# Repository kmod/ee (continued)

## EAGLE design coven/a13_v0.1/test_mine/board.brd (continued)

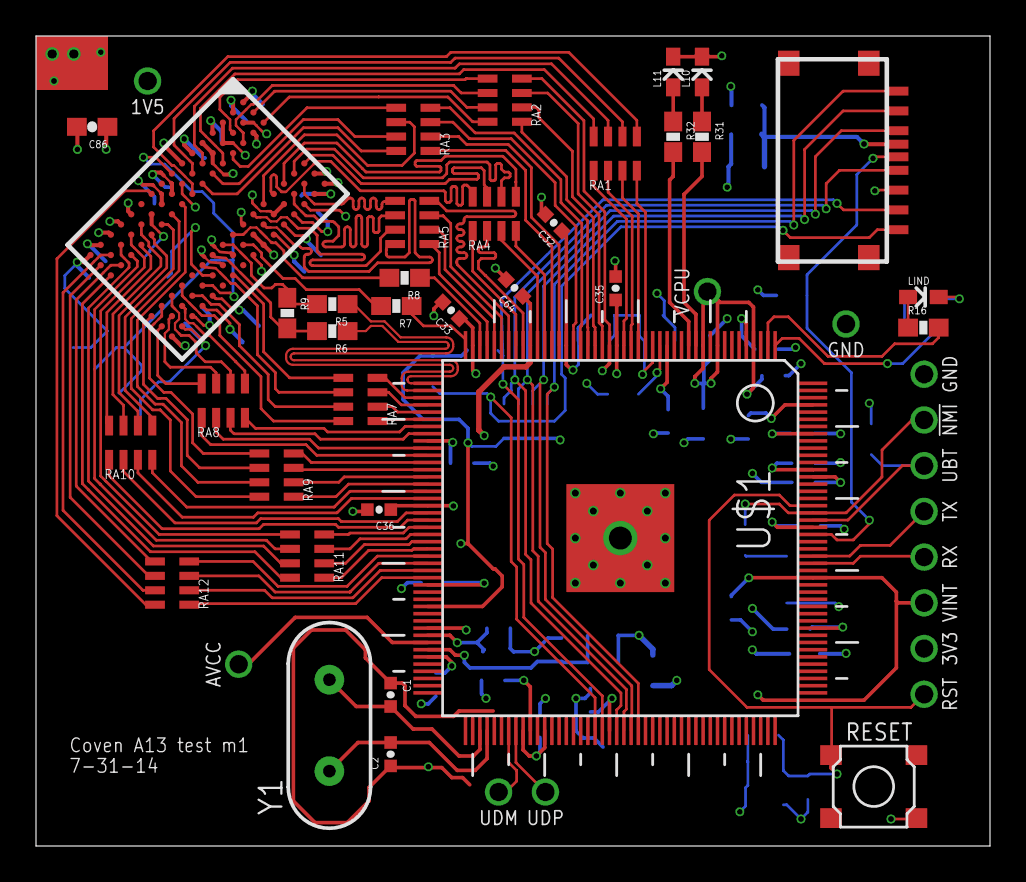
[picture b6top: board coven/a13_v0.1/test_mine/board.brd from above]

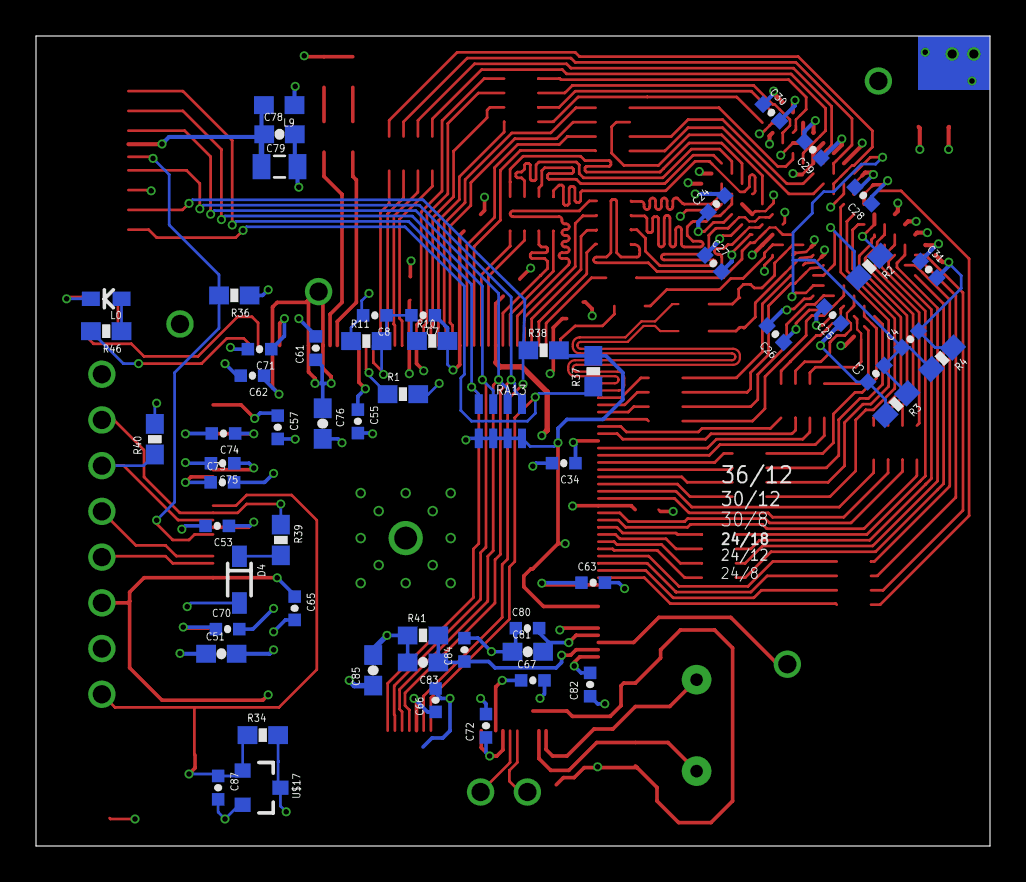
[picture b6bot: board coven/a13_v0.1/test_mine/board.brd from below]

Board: 4 copper layers, 53.0 x 45.0 mm, 108 parts (58 on the bottom side), 135 nets.

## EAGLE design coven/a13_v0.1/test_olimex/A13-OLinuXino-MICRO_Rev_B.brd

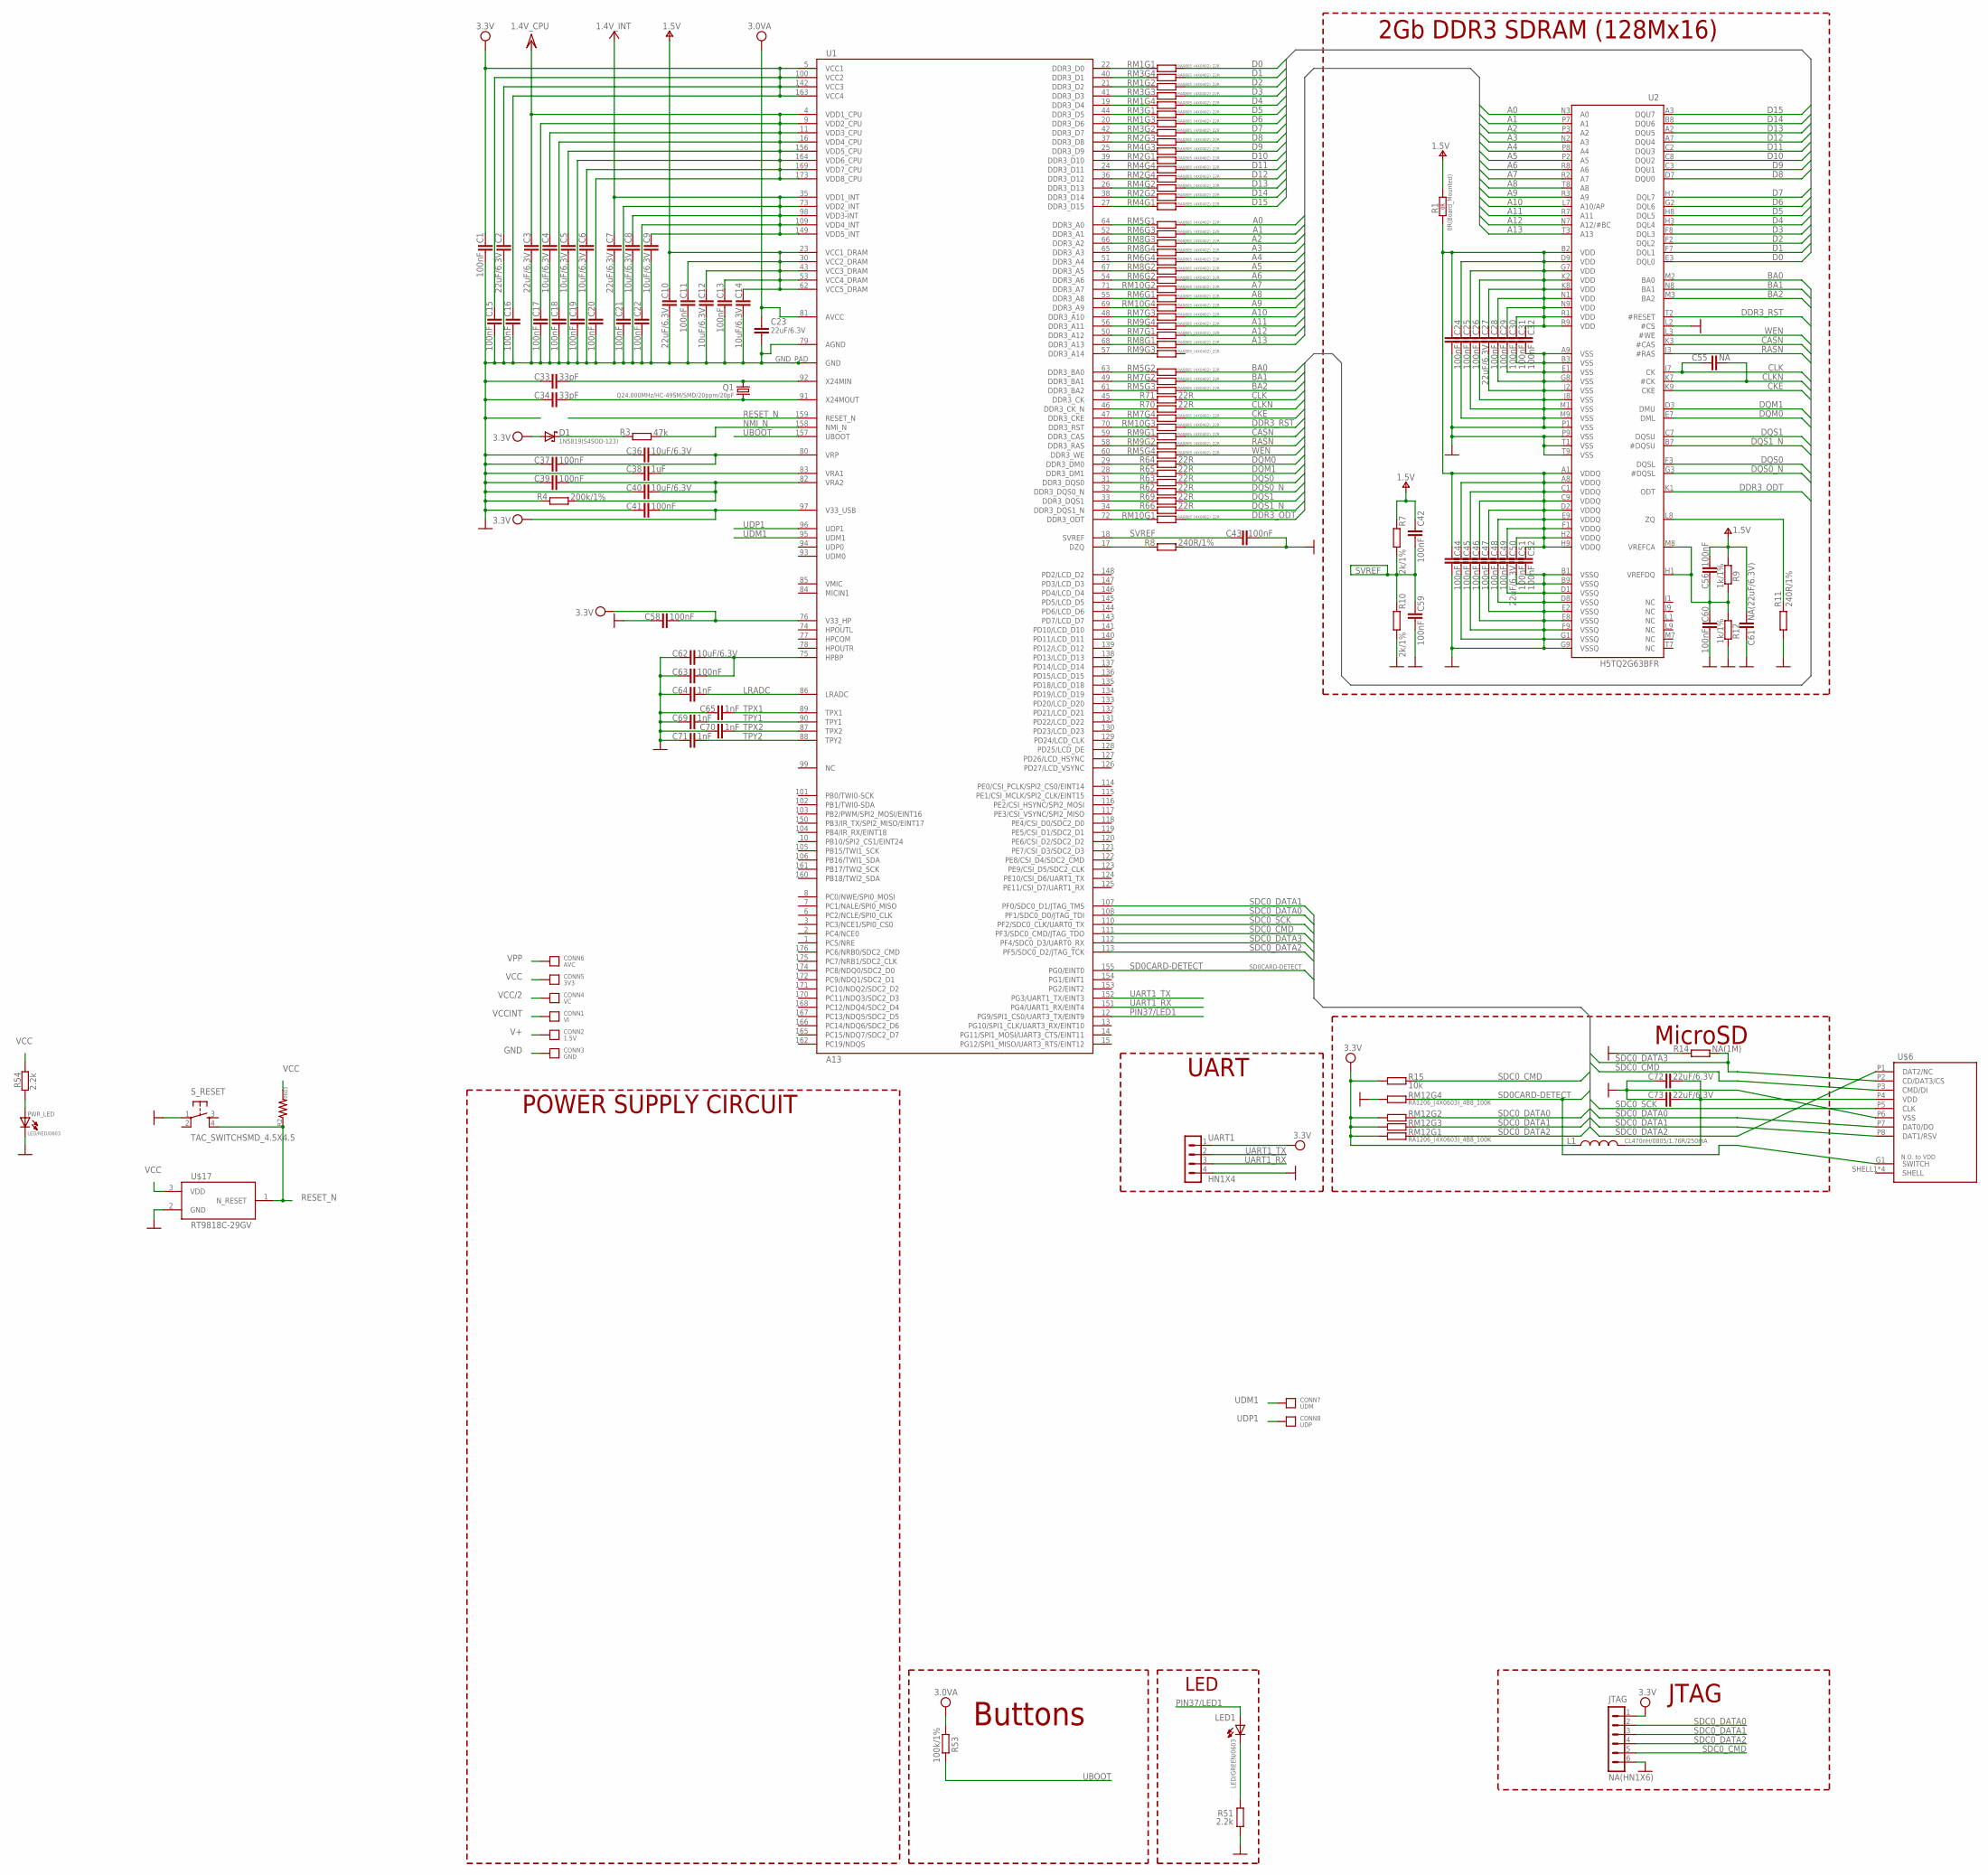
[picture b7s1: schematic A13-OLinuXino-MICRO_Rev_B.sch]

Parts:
C1, C11, C13, C15, C16, C17, C18, C19, C20, C21, C22, C24, C25, C26, C28, C29, C30, C31, C32, C37, C39, C41, C42, C43, C44, C45, C46, C47, C48, C49, C51, C52, C56, C58, C59, C60, C63: 100nF; C0402
C2, C3, C7, C10, C23, C27, C50, C72, C73: 22uF/6.3V; C0603_DWS
C4, C5, C6, C8, C9, C12, C14, C36, C40, C62: 10uF/6.3V; C0603_DWS
C33, C34: 33pF; C0402
C38: 1uF; C0402
C55: NA; C0603_DWS
C61: NA(22uF/6.3V); C0603_DWS
C64, C65, C69, C70, C71: 1nF; C0402
CONN1: VI; HOLE_22AWG
CONN2: 1.5V; HOLE_22AWG
CONN3: GND; HOLE_22AWG
CONN4: VC; HOLE_22AWG
CONN5: 3V3; HOLE_22AWG
CONN6: AVC; HOLE_22AWG
CONN7: UDM; HOLE_22AWG
CONN8: UDP; HOLE_22AWG
D1: 1N5819(S4SOD-123); SOD-123
JTAG: NA(HN1X6); HN1X6
L1: CL470nH/0805/1.76R/250mA; L0805_5MIL_DWS
LED1: LED/GREEN/0603; LED-0603
PWR_LED: LED/RED/0603; LED-0603
Q1: Q24.000MHz/HC-49SM/SMD/20ppm/20pF; HC49/SMD2_THIN
R1: 0R(Board_Mounted); 0603_0R
R2: RESISTOR0603; 0603-RES
R3: 47k; R0603_5MIL_DWS
R4: 200k/1%; R0603_5MIL_DWS
R7, R10: 2k/1%; R0603_5MIL_DWS
R8, R11: 240R/1%; R0603_5MIL_DWS
R9, R12: 1k/1%; R0603_5MIL_DWS
R14: NA(1M); R0603_5MIL_DWS
R15: 10k; R0603_5MIL_DWS
R51, R54: 2.2k; R0603_5MIL_DWS
R53: 100k/1%; R0603_5MIL_DWS
R62, R63, R64, R65, R66, R69, R70, R71: 22R; R0603_5MIL_DWS
RM1, RM2, RM3, RM4, RM5, RM6, RM7, RM8, RM9, RM10: RA0805_(4X0402)_22R; R_MATRIX_4_0402_25X625
RM12: RA1206_(4X0603)_4B8_100K; R_MATRIX_4
S_RESET: TAC_SWITCHSMD_4.5X4.5; TAC_SWITCH_SMD_4.5X4.5
U1: A13; TQFP176
U2: H5TQ2G63BFR; FBGA96
U$6: MICROSDMOLEX-1050270001; MICROSD-MOLEX-1050270001
U$17: RT9818C-29GV; SOT23-3
UART1: HN1X4

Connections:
A0: RM5.1.2 (2), U2.N3 (A0)
A1: RM6.3.2 (2), U2.P7 (A1)
A2: RM8.3.2 (2), U2.P3 (A2)
A3: RM8.4.2 (2), U2.N2 (A3)
A4: RM6.4.2 (2), U2.P8 (A4)
A5: RM8.2.2 (2), U2.P2 (A5)
A6: RM6.2.2 (2), U2.R8 (A6)
A7: RM10.2.2 (2), U2.R2 (A7)
A8: RM6.1.2 (2), U2.T8 (A8)
A9: RM10.4.2 (2), U2.R3 (A9)
A10: RM7.3.2 (2), U2.L7 (A10/AP)
A11: RM9.4.2 (2), U2.R7 (A11)
A12: RM7.1.2 (2), U2.N7 (A12/#BC)
A13: RM8.1.2 (2), U2.T3 (A13)
BA0: RM5.2.2 (2), U2.M2 (BA0)
BA1: RM7.2.2 (2), U2.N8 (BA1)
BA2: RM5.3.2 (2), U2.M3 (BA2)
CASN: RM9.1.2 (2), U2.K3 (#CAS)
CKE: RM7.4.2 (2), U2.K9 (CKE)
CLK: C55.1, R71.1, U2.J7 (CK)
CLKN: C55.2, R70.1, U2.K7 (#CK)
D0: RM1.1.2 (2), U2.E3 (DQL0)
D1: RM3.4.2 (2), U2.F7 (DQL1)
D2: RM1.2.2 (2), U2.F2 (DQL2)
D3: RM3.3.2 (2), U2.F8 (DQL3)
D4: RM1.4.2 (2), U2.H3 (DQL4)
D5: RM3.1.2 (2), U2.H8 (DQL5)
D6: RM1.3.2 (2), U2.G2 (DQL6)
D7: RM3.2.2 (2), U2.H7 (DQL7)
D8: RM2.3.2 (2), U2.D7 (DQU0)
D9: RM4.3.2 (2), U2.C3 (DQU1)
D10: RM2.1.2 (2), U2.C8 (DQU2)
D11: RM4.4.2 (2), U2.C2 (DQU3)
D12: RM2.4.2 (2), U2.A7 (DQU4)
D13: RM4.2.2 (2), U2.A2 (DQU5)
D14: RM2.2.2 (2), U2.B8 (DQU6)
D15: RM4.1.2 (2), U2.A3 (DQU7)
DDR3_A0: RM5.1.1 (1), U1.64 (DDR3_A0)
DDR3_A1: RM6.3.1 (1), U1.52 (DDR3_A1)
DDR3_A2: RM8.3.1 (1), U1.66 (DDR3_A2)
DDR3_A3: RM8.4.1 (1), U1.65 (DDR3_A3)
DDR3_A4: RM6.4.1 (1), U1.51 (DDR3_A4)
DDR3_A5: RM8.2.1 (1), U1.67 (DDR3_A5)
DDR3_A6: RM6.2.1 (1), U1.54 (DDR3_A6)
DDR3_A7: RM10.2.1 (1), U1.71 (DDR3_A7)
DDR3_A8: RM6.1.1 (1), U1.55 (DDR3_A8)
DDR3_A9: RM10.4.1 (1), U1.69 (DDR3_A9)
DDR3_A10: RM7.3.1 (1), U1.48 (DDR3_A10)
DDR3_A11: RM9.4.1 (1), U1.56 (DDR3_A11)
DDR3_A12: RM7.1.1 (1), U1.50 (DDR3_A12)
DDR3_A13: RM8.1.1 (1), U1.68 (DDR3_A13)
DDR3_A14: RM9.3.1 (1), U1.57 (DDR3_A14)
DDR3_BA0: RM5.2.1 (1), U1.63 (DDR3_BA0)
DDR3_BA1: RM7.2.1 (1), U1.49 (DDR3_BA1)
DDR3_BA2: RM5.3.1 (1), U1.61 (DDR3_BA2)
DDR3_CAS: RM9.1.1 (1), U1.59 (DDR3_CAS)
DDR3_CK: R71.2, U1.45 (DDR3_CK)
DDR3_CKE: RM7.4.1 (1), U1.47 (DDR3_CKE)
DDR3_CK_N: R70.2, U1.46 (DDR3_CK_N)
DDR3_D0: RM1.1.1 (1), U1.22 (DDR3_D0)
DDR3_D1: RM3.4.1 (1), U1.40 (DDR3_D1)
DDR3_D2: RM1.2.1 (1), U1.21 (DDR3_D2)
DDR3_D3: RM3.3.1 (1), U1.41 (DDR3_D3)
DDR3_D4: RM1.4.1 (1), U1.19 (DDR3_D4)
DDR3_D5: RM3.1.1 (1), U1.44 (DDR3_D5)
DDR3_D6: RM1.3.1 (1), U1.20 (DDR3_D6)
DDR3_D7: RM3.2.1 (1), U1.42 (DDR3_D7)
DDR3_D8: RM2.3.1 (1), U1.37 (DDR3_D8)
DDR3_D9: RM4.3.1 (1), U1.25 (DDR3_D9)
DDR3_D10: RM2.1.1 (1), U1.39 (DDR3_D10)
DDR3_D11: RM4.4.1 (1), U1.24 (DDR3_D11)
DDR3_D12: RM2.4.1 (1), U1.36 (DDR3_D12)
DDR3_D13: RM4.2.1 (1), U1.26 (DDR3_D13)
DDR3_D14: RM2.2.1 (1), U1.38 (DDR3_D14)
DDR3_D15: RM4.1.1 (1), U1.27 (DDR3_D15)
DDR3_DM0: R64.2, U1.29 (DDR3_DM0)
DDR3_DM1: R65.2, U1.28 (DDR3_DM1)
DDR3_DQS0: R63.2, U1.31 (DDR3_DQS0)
DDR3_DQS0_N: R62.2, U1.32 (DDR3_DQS0_N)
DDR3_DQS1: R69.2, U1.33 (DDR3_DQS1)
DDR3_DQS1_N: R66.2, U1.34 (DDR3_DQS1_N)
DDR3_ODT: RM10.1.2 (2), U2.K1 (ODT)
DDR3_ODTT: RM10.1.1 (1), U1.72 (DDR3_ODT)
DDR3_RAS: RM9.2.1 (1), U1.58 (DDR3_RAS)
DDR3_RST: RM10.3.2 (2), U2.T2 (#RESET)
DDR3_RSTT: RM10.3.1 (1), U1.70 (DDR3_RST)
DDR3_WE: RM5.4.1 (1), U1.60 (DDR3_WE)
DQM0: R64.1, U2.E7 (DML)
DQM1: R65.1, U2.D3 (DMU)
DQS0: R63.1, U2.F3 (DQSL)
DQS0_N: R62.1, U2.G3 (#DQSL)
DQS1: R69.1, U2.C7 (DQSU)
DQS1_N: R66.1, U2.B7 (#DQSU)
DZQ: R8.2, U1.17 (DZQ)
GND: C1.1, C2.1, C3.1, C4.1, C5.1, C6.1, C7.1, C8.1, C9.1, C10.1, C11.1, C12.1, C13.1, C14.1, C15.1, C16.1, C17.1, C18.1, C19.1, C20.1, C21.1, C22.1, C23.1, C24.2, C25.2, C26.2, C27.2, C28.2, C29.2, C30.2, C31.2, C32.2, C33.1, C34.1, C36.1, C37.1, C38.1, C39.1, C40.1, C41.1, C43.1, C44.2, C45.2, C46.2, C47.2, C48.2, C49.2, C50.2, C51.2, C52.2, C58.1, C59.1, C60.1, C61.1, C62.1, C63.1, C64.1, C65.1, C69.1, C70.1, C71.1, C72.1, C73.1, CONN3.P, JTAG.6, PWR_LED.C, R4.2, R8.1, R10.1, R11.1, R12.1, R14.2, R51.1, RM12.4.1 (1), S_RESET.1, U1.79 (AGND), U1.GND_PAD (GND), U1.P$2 (GND), U1.P$3 (GND), U1.P$4 (GND), U1.P$5 (GND), U1.P$6 (GND), U1.P$7 (GND), U1.P$8 (GND), U1.P$9 (GND), U1.P$10 (GND), U1.P$11 (GND), U1.P$12 (GND), U1.P$13 (GND), U1.P$14 (GND), U1.P$15 (GND), U1.P$16 (GND), U1.P$17 (GND), U1.P$18 (GND), U2.A9 (VSS), U2.B1 (VSSQ), U2.B3 (VSS), U2.B9 (VSSQ), U2.D1 (VSSQ), U2.D8 (VSSQ), U2.E1 (VSS), U2.E2 (VSSQ), U2.E8 (VSSQ), U2.F9 (VSSQ), U2.G1 (VSSQ), U2.G8 (VSS), U2.G9 (VSSQ), U2.J2 (VSS), U2.J8 (VSS), U2.L2 (#CS), U2.M1 (VSS), U2.M9 (VSS), U2.P1 (VSS), U2.P9 (VSS), U2.T1 (VSS), U2.T9 (VSS), U$6.P6 (VSS), U$17.2 (GND), UART1.4
LRADC: C64.2, U1.86 (LRADC)
unnamed: C62.2, C63.2, U1.75 (HPBP)
unnamed: C36.2, C37.2, U1.80 (VRP)
unnamed: D1.C, R3.2
unnamed: C38.2, U1.83 (VRA1)
unnamed: C39.2, C40.2, R4.1, U1.82 (VRA2)
unnamed: C56.2, C60.2, R9.1, R12.2, U2.H1 (VREFDQ), U2.M8 (VREFCA)
unnamed: LED1.C, R51.2
unnamed: PWR_LED.A, R54.2
NMI_N: R3.1, U1.158 (NMI_N)
PIN37/LED1: LED1.A, U1.12 (PG9/SPI1_CS0/UART3_TX/EINT9)
RASN: RM9.2.2 (2), U2.J3 (#RAS)
RESET_N: R2.1, S_RESET.4, U1.159 (RESET_N), U$17.1 (N_RESET)
SD0CARD-DETECT: RM12.4.2 (2), U1.155 (PG0/EINT0), U$6.G1 (SWITCH)
SDC0_CMD: JTAG.5, R15.1, U1.111 (PF3/SDC0_CMD/JTAG_TDO), U$6.P3 (CMD/DI)
SDC0_DATA0: JTAG.2, RM12.2.1 (1), U1.108 (PF1/SDC0_D0/JTAG_TDI), U$6.P7 (DAT0/DO)
SDC0_DATA1: JTAG.3, RM12.3.1 (1), U1.107 (PF0/SDC0_D1/JTAG_TMS), U$6.P8 (DAT1/RSV)
SDC0_DATA2: JTAG.4, RM12.1.1 (1), U1.113 (PF5/SDC0_D2/JTAG_TCK), U$6.P1 (DAT2/NC)
SDC0_DATA3: R14.1, U1.112 (PF4/SDC0_D3/UART0_RX), U$6.P2 (CD/DAT3/CS)
SDC0_SCK: U1.110 (PF2/SDC0_CLK/UART0_TX), U$6.P5 (CLK)
SD_VCC: C72.2, C73.2, L1.2, U$6.P4 (VDD)
SVREF: C42.2, C43.2, C59.2, R7.1, R10.2, U1.18 (SVREF)
TPX1: C65.2, U1.89 (TPX1)
TPX2: C70.2, U1.87 (TPX2)
TPY1: C69.2, U1.90 (TPY1)
TPY2: C71.2, U1.88 (TPY2)
UART1_RX: U1.151 (PG4/UART1_RX/EINT4), UART1.3
UART1_TX: U1.152 (PG3/UART1_TX/EINT3), UART1.2
UBOOT: R53.2, U1.157 (UBOOT)
UDM1: CONN7.P, U1.95 (UDM1)
UDP1: CONN8.P, U1.96 (UDP1)
V+: C10.2, C11.2, C12.2, C13.2, C14.2, C42.1, C56.1, C61.2, CONN2.P, R1.1 (1.1), R7.2, R9.2, U1.23 (VCC1_DRAM), U1.30 (VCC2_DRAM), U1.43 (VCC3_DRAM), U1.53 (VCC4_DRAM), U1.62 (VCC5_DRAM)
VCC: C1.2, C2.2, C15.2, C16.2, C41.2, C58.2, CONN5.P, D1.A, JTAG.1, L1.1, R2.2, R15.2, R54.1, RM12.1.2 (2), RM12.2.2 (2), RM12.3.2 (2), U1.5 (VCC1), U1.76 (V33_HP), U1.97 (V33_USB), U1.100 (VCC2), U1.142 (VCC3), U1.163 (VCC4), U$17.3 (VDD), UART1.1
VCC/2: C3.2, C4.2, C5.2, C6.2, C17.2, C18.2, C19.2, C20.2, CONN4.P, U1.4 (VDD1_CPU), U1.9 (VDD2_CPU), U1.11 (VDD3_CPU), U1.16 (VDD4_CPU), U1.156 (VDD5_CPU), U1.164 (VDD6_CPU), U1.169 (VDD7_CPU), U1.173 (VDD8_CPU)
VCCINT: C7.2, C8.2, C9.2, C21.2, C22.2, CONN1.P, U1.35 (VDD1_INT), U1.73 (VDD2_INT), U1.98 (VDD3-INT), U1.109 (VDD4_INT), U1.149 (VDD5_INT)
VDD.: C24.1, C25.1, C26.1, C27.1, C28.1, C29.1, C30.1, C31.1, C32.1, C44.1, C45.1, C46.1, C47.1, C48.1, C49.1, C50.1, C51.1, C52.1, R1.2 (1.2), U2.A1 (VDDQ), U2.A8 (VDDQ), U2.B2 (VDD), U2.C1 (VDDQ), U2.C9 (VDDQ), U2.D2 (VDDQ), U2.D9 (VDD), U2.E9 (VDDQ), U2.F1 (VDDQ), U2.G7 (VDD), U2.H2 (VDDQ), U2.H9 (VDDQ), U2.K2 (VDD), U2.K8 (VDD), U2.N1 (VDD), U2.N9 (VDD), U2.R1 (VDD), U2.R9 (VDD)
VMIC: U1.85 (VMIC)
VPP: C23.2, CONN6.P, R53.1, U1.81 (AVCC)
WEN: RM5.4.2 (2), U2.L3 (#WE)
XTALI: C33.2, Q1.2, U1.92 (X24MIN)
XTALO: C34.2, Q1.1, U1.91 (X24MOUT)
ZQ: R11.2, U2.L8 (ZQ)

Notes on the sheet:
POWER SUPPLY CIRCUIT
MicroSD
Buttons
LED
2Gb DDR3 SDRAM (128Mx16)
JTAG
UART

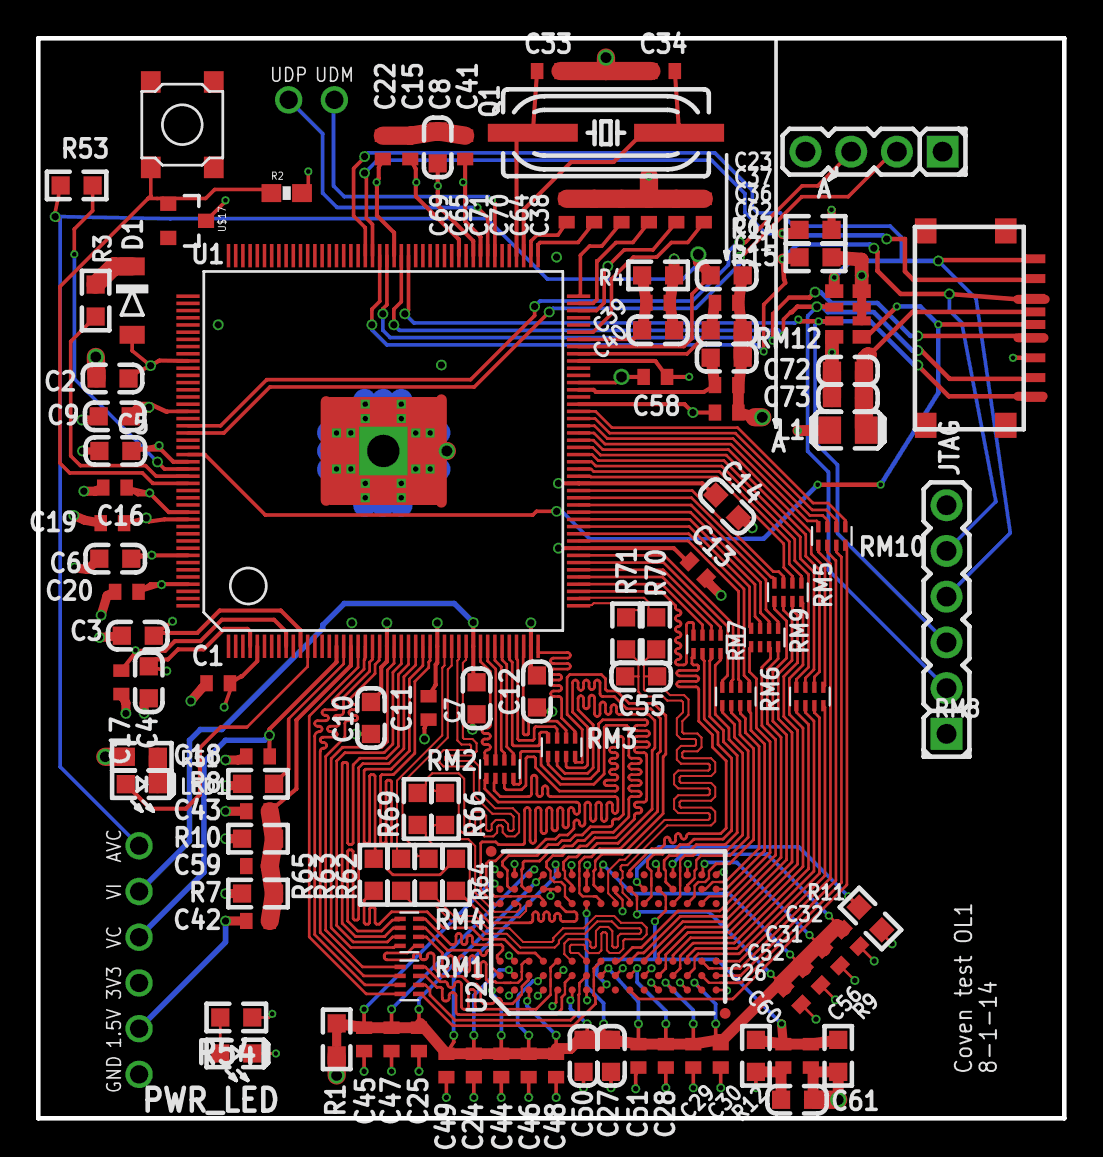
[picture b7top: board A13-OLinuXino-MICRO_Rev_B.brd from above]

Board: 4 copper layers, 57.0 x 60.0 mm, 120 parts (0 on the bottom side), 136 nets.
